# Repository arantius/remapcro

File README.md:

The remapcro is a hardware device for storing and replaying keyboard macros.

For more detail see: https://making.arantius.com/remapcro

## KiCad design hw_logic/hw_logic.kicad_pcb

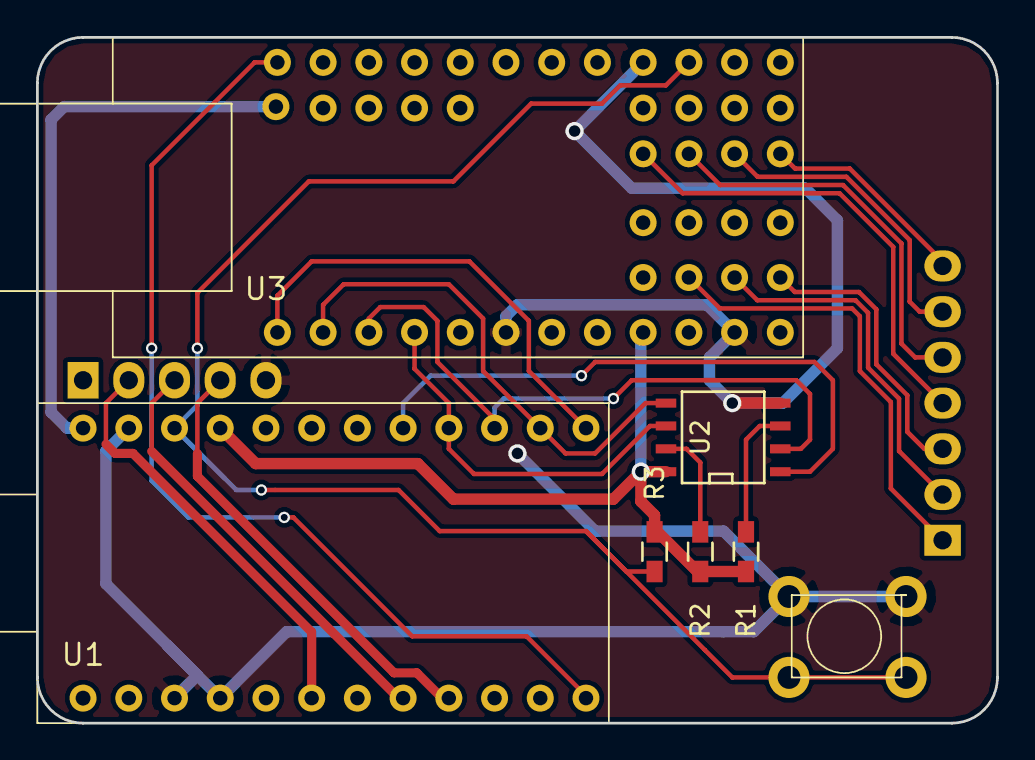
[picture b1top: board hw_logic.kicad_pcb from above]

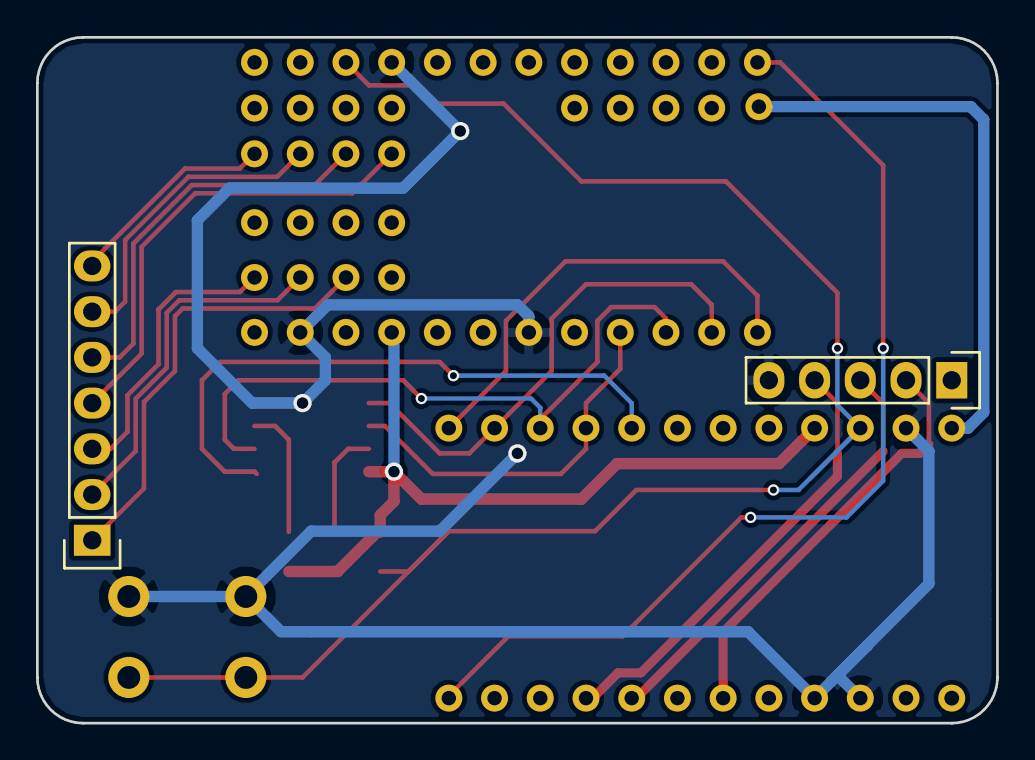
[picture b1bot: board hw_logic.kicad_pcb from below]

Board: 2 copper layers, 53.3 x 38.1 mm, 9 parts (2 on the bottom side), 22 nets.

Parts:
P1: CONN_01X05; Pin_Header_Straight_1x05
P2: CONN_01X07; Pin_Header_Straight_1x07
R1, R2, R3: 4k7; R_0603_HandSoldering
SW13: SW_PUSH; SW_TACTILE_THT
U1: LEO_PRO_MICRO
U2: IS25LQ; SOIC-8-N
U3: USB_HOST_SHIELD_MINI; UHS_MINI

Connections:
+3V3: R1.1, R2.1, R3.1, U1.21, U2.8, U3.9
+5V: U1.24, U3.25
/FLASH_SS: U1.17, U2.1
/GI0: P2.3, U3.30
/GI1: P2.2, U3.31
/GI2: P2.1, U3.32
/GO0: P2.7, U3.38
/GO1: P2.6, U3.39
/GO2: P2.5, U3.40
/GO3: P2.4, U3.41
/LED_B: P1.2, U1.6
/LED_G: P1.3, U1.8
/LED_R: P1.4, U1.9
/MISO: U1.15, U2.2, U3.3
/MOSI: U1.14, U2.5, U3.2
/RST: R3.2, SW13.1, U1.22, U3.15
/SCK: U1.16, U2.6, U3.4
/USB_INT: U1.12, U3.24
/USB_SS: U1.13, U3.1
GND: P1.5, SW13.2, U1.3, U1.4, U1.23, U2.4, U3.6, U3.11, U3.16
unnamed: R1.2, U2.3
unnamed: R2.2, U2.7

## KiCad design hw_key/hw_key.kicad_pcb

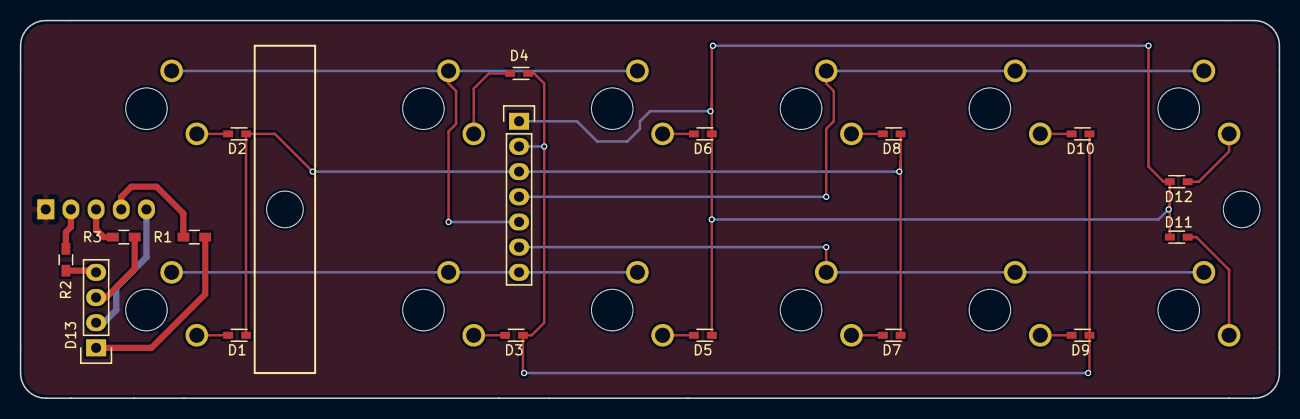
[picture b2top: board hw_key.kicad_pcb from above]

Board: 2 copper layers, 127.0 x 38.1 mm, 30 parts (1 on the bottom side), 26 nets.

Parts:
D1, D2, D3, D4, D5, D6, D7, D8, D9, D10, D11, D12: D; SOD-523-handsoldering
D13: LED_RABG; Pin_Header_Straight_1x04
P1: CONN_01X07; Pin_Header_Straight_1x07
P2: CONN_01X05; Pin_Header_Straight_1x05
R1, R2, R3: 330; R_0603_HandSoldering
SW1, SW2, SW3, SW4, SW5, SW6, SW7, SW8, SW9, SW10, SW11, SW12: SW_PUSH_SMALL_H; CHERRY_MX

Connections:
+3V3: D13.2, P2.5
/LED_B: P2.2, R2.2
/LED_G: P2.3, R3.2
/LED_R: P2.4, R1.2
/kC0: P1.7, SW1.1, SW3.1, SW5.1
/kC1: P1.6, SW7.1, SW9.1, SW11.1
/kC2: P1.5, SW2.1, SW4.1, SW6.1
/kC3: P1.4, SW8.1, SW10.1, SW12.1
/kR0: D1.1, D2.1, D7.1, D8.1, P1.3
/kR1: D3.1, D4.1, D9.1, D10.1, P1.2
/kR2: D5.1, D6.1, D11.1, D12.1, P1.1
unnamed: D1.2, SW1.2
unnamed: D2.2, SW2.2
unnamed: D3.2, SW3.2
unnamed: D4.2, SW4.2
unnamed: D5.2, SW5.2
unnamed: D6.2, SW6.2
unnamed: D7.2, SW7.2
unnamed: D8.2, SW8.2
unnamed: D9.2, SW9.2
unnamed: D10.2, SW10.2
unnamed: D11.2, SW11.2
unnamed: D12.2, SW12.2
unnamed: D13.1, R1.1
unnamed: D13.3, R3.1
unnamed: D13.4, R2.1

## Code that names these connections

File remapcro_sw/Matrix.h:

#define MATRIX_POLL_PERIOD 16
#define MATRIX_MACRO 0

// When storing a macro on a key from the "real" keyboard, we use the HID
// ID of its key to store the macro sector (in EEPROM).  When storing the
// macro sector for a matrix key, we want to use an ID that won't conflict
// with those "real" keys.  There's just one byte, and most of the
// possible values are taken.  The space for F13 through F24 starts at
// 0x68 and we have twelve (well, eleven ...) possible matrix keys.
// Seems like a perfect space to reuse.
#define MATRIX_MACRO_OFFSET 0x68


#define PIN_LED_R 6
#define PIN_LED_G 5
#define PIN_LED_B 3

enum class LedColor : byte { off, red, green, blue, yellow };

uint8_t ledBlinking = 0;
LedColor ledColor = LedColor::off;


void initMatrix();
void keyMatrixRead();
void lightLed(LedColor c);

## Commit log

2016-08-16 Initial basic USB host demo.
    Just dumps HID data to Serial, and twiddles LEDs.
2016-08-20 esp compatible baud rate
2016-08-20 two-part basic data shunt
2016-08-20 successful data pass thru to keyboard!
2016-09-10 Independent software.
    Forwards USB keyboard, reads and prints matrix.
2016-09-10 USB host and key matrix step 1
    USB keyboard is proxied, matrix is read, both emit key event debugging.
2016-09-10 Both keyboards are proxied
2016-09-10 shorter file name
2016-09-10 More dev-only output.
2016-09-10 send error reports
2016-09-22 Beginning framework for macro recording.
2016-09-28 various small cleanups
2016-09-28 prep for storing macros
2016-10-14 Flash string macros.
2016-10-14 Begin layout for raw flash chip I/O.
2016-10-16 record and store macro data
2016-10-16 read/dump to serial macro data, other debugging cmds
2016-10-16 repeat * cancels macro record
2016-10-16 replay macros
2016-10-16 handle keypress simplification
2016-12-12 macro-during-macro bug fix
2016-12-16 first hardware commit
    component for UHS mini
2016-12-16 erase new "unused" sectors as they are selected
2016-12-16 repair macro saves and lookups, modifiers, replay
2016-12-16 faster replay, light led during
2016-12-16 enhanced serial debugging commands
2016-12-16 don't wait forever for serial
    wait a little while, in case I'm really interested, but give up so the
    keyboard features will work even if I never open the serial port
2016-12-16 start message first
2016-12-16 Correctly initialize reportErr.
2016-12-16 debug command for dumping current report
2016-12-16 Remove unused KeyEvent struct
2016-12-16 add some footprints, bare schematic
2016-12-16 UsbDev: specific enable-debugging-define
2016-12-16 tiny schematic tweaks
2016-12-16 cherry mx switches added
2016-12-16 fix uhs mini footprint pin numbers
2016-12-16 circular pads
2016-12-16 rst switch, pcb layout
2016-12-16 more pcb layout
    probably fab as two separate boards!
2016-12-16 pin/net fixes
    custom component, bad definitions
2016-12-29 tweaks including hand-solderable SMD diode
2016-12-29 Split logic & key boards to separate projects.
2016-12-29 misc, rst button 3d model
2016-12-29 clean up traces, ground fills
2017-01-01 mounting holes
2017-01-01 resolve mysterious scope problem
2017-01-02 move usb init to relevant file
2017-01-02 correct pin layouts
    as per breadboard test
2017-01-02 hole position, corner rounding size
2017-01-04 revamp boards (for assembled height)
    flip logic over so that it can mate closely with key; reset button moves
    to same side as all the other parts; board assembly down to ~16mm high
    and assembly more easily lends itself to angling for even less height at
    the front for slightly more in the back
2017-01-07 final PCB revisions
    plus the start of a case to hold them
2017-01-20 case designs in three and two parts
    for 3D printing
2017-01-20 Notes from first assembly.
    Issues discovered + tweaked LED current limiting resistors based on observation. (Duh, the colors have different forward voltages, need different resistor values.)
2017-01-20 Update for real hardware.
    * Key layout: two columns of six keys.
    * Pins for LED and chip enable(s).
    * (Basic) RGB led support.
    * Flash chip test output at init.
2017-01-20 more consistent DBG define naming
2017-01-21 tweaked case files
    fits the original misaligned PCB, except I had to cut a bit off the
    bottom of the back piece (!?)
    measuring along the height of the back of the main case I get 30.4mm
    with my calipers, but the sketchu model height is 31.9 -- 1.5mm more,
    just about exactly what I cut off.
    hard to explain; my 3d printer's Z is miscalibrated?
2017-01-21 Wrap all debug defines with a global one.
    Also disable all of them with it.
2017-01-21 init() for flash and host both act similarly
2017-01-24 Always include serial commands.
2017-01-24 Init KeyboardPlus in UsbDev::init().
    It's part of being the USB device, after all.
2017-01-24 Don't twiddle the built in LED on USB activity.
2017-01-24 syntax error: missing close paren
2017-01-24 Rename handleMacroKey() for clarity.
    It handles all keys, during recording. Not the macro key itself.
2017-01-24 Allow erasing a macro.
    By recording one with no length, if a key was selected.
2017-01-28 UsbHost: check for press and release in one loop.
2017-01-28 Use UHS shield library's keyboard parser.
    Turn off its debugging, as this part is very verbose.
2017-01-28 Simpler/more efficient keyboard report generation.
    It's okay to mix nulls and values, so don't put effort into shuffling the values all to the front/nulls to the back.
2017-01-28 More efficient macro replay.
    Like when generating interactive reports, don't obsess about putting all the values in the front of the buffer.
2017-01-28 Parameterize block read size during macro replay.
2017-01-28 Larger flash block read size during macro replay.
2017-01-28 Disable serial debugging output.
2017-01-29 OpenSCAD case.
    Beginnings.
2017-01-29 Media key notes.
2017-01-29 Macro replay speed tweak.
2017-01-29 More case details.
    Holes in mock key PCB, peg and support line up, PCB to module.
2017-01-29 Case top: misaligned PCB workaround, bottom place inset.
2017-01-29 rename key_pcb.scad -> pcbs.scad
2017-01-29 Case: Also model logic PCB position.
2017-01-29 Logic PCB: Fix connector P2 position, swap LED power line.
    A better fix would also swap around the LED on the "key" board, but this reduces bodge needs without respinning that board.
2017-01-29 Sub-boards on silkscreen layer.
2017-01-29 Remove sketchup based case models.
2017-01-30 Finish bottom, including holes.
2017-01-30 tweak bottom overhang, generate STLs
2017-01-30 Fix screw head hole, broken by height adjustment.
2017-02-14 Only enter modifier mode when not in it.
2017-02-14 Properly release keys in macro replay.
    If the order is ABABBB that means: press A, press B, release A, release B, press B, release B.
    Before this, the second B would be pressed into the slot just released for the A, rather than releasing the existing pressed B.
2017-03-20 Revert "Remove sketchup based case models."
    At least for my first skewed boards, it might still work better.
2017-03-20 Remove verbose media key notes.
2017-03-20 Add license.
2017-03-20 Add readme.
